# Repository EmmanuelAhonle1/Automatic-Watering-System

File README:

# Automatic Watering System

## Overview

The Automatic Watering System is a smart IoT solution for plant care, built using ESP8266 microcontrollers. The system provides automated plant monitoring and watering capabilities with a web-based interface for configuration and monitoring.

## Hardware Components

- ESP8266 Microcontroller
- DHT11 Temperature and Humidity Sensor (Pin D5)
- Capacitive Soil Moisture Sensor (Pin D6)
- VEML7700 Ambient Light Sensor (Pin D7)
- LC709203F Battery Level Sensor (Pin D4)
- RGB Status LED (Pins D0, D1, D2)
- All components are defined in `Pinouts.hpp`

## Features

### 1. WiFi Configuration and Management

- Captive portal for initial WiFi setup
- Automatic reconnection handling
- OTA (Over-the-Air) update support
- Access Point mode with DNS server for initial configuration
- Support for multiple network security types

### 2. Device Management

- Unique device naming system
- Persistent storage of device settings
- MAC address tracking
- JSON-based configuration storage

### 3. Sensor Integration

- Temperature and humidity monitoring
- Soil moisture level detection
- Ambient light measurement
- Battery level monitoring
- All sensor readings available through unified interface

### 4. Status Indication

RGB LED status indicators for:

- WiFi Connected (Blinking Blue)
- AP Mode (Solid Red)
- MySQL Server Connected (Solid Green)
- Connection Lost (Fast Red Blinking)
- Reconnecting (Purple Blinking)

### 5. Web Interface

Three main interfaces:

1. WiFi Configuration (`/wifi_config/`)

   - Network scanning
   - Connection management
   - Status display

2. User Authentication (`/intro_login/`)

   - User login
   - New user registration
   - Session management

3. Plant Registration (`/plant_registration/`)
   - Plant node configuration
   - Species selection
   - Customizable care parameters

## Software Architecture

### Core Components

1. **WiFi Manager** (`wifi_manager.hpp`, `wifi_manager.cpp`)

   - Handles all network connectivity
   - Manages access point and station modes
   - Implements captive portal
   - Handles OTA updates

2. **Device Manager** (`device_manager.hpp`, `device_manager.cpp`)

   - Manages device identification
   - Handles configuration storage
   - Coordinates settings updates

3. **Data Acquisition** (`dataAcquisition.hpp`, `dataAcquisition.cpp`)

   - Interfaces with all sensors
   - Provides unified data reading interface
   - Handles sensor calibration and thresholds

4. **Database Communication** (`DatabaseCommands.hpp`, `DatabaseCommands.cpp`)

   - Manages API interactions
   - Handles data synchronization
   - Implements connection monitoring

5. **RGB Status Handler** (`rgb_status.hpp`, `rgb_status.cpp`)
   - Manages visual feedback
   - Implements state machine for status indication
   - Handles LED control

### Web Interface

The system provides three main web interfaces:

1. **WiFi Configuration**

   - Network scanning and selection
   - Password input
   - Connection status display

2. **User Authentication**

   - Login interface
   - Registration form
   - Session management

3. **Plant Registration**
   - Plant species selection
   - Watering frequency configuration
   - Environmental threshold settings

## Setup and Configuration

### Initial Setup

1. Flash the ESP8266 with the firmware
2. Power on the device
3. Connect to the device's AP (Format: "PlantNode-XXXX")
4. Navigate to the captive portal
5. Configure WiFi settings

### Plant Registration

1. Login or create an account
2. Configure plant parameters:
   - Node name
   - Plant species
   - Watering frequency
   - Environmental thresholds
3. Save configuration

## API Integration

The system integrates with a REST API for:

- User authentication
- Plant node registration
- Settings synchronization
- Data logging

API endpoints are defined in `dbQueryCreator.hpp` and configured via `config.h`

## Development

### Requirements

- Arduino IDE or PlatformIO
- ESP8266 board support
- Required Libraries:
  - ESP8266WiFi
  - ESP8266WebServer
  - ArduinoJson
  - DHT sensor library
  - VEML7700 library
  - LC709203F library
  - RGBLed library

### Building

1. Clone the repository
2. Install required libraries
3. Configure `config.h` with API credentials
4. Build and flash to ESP8266

## Security Features

- Secure WiFi configuration
- Password protection
- Session management
- API authentication
- OTA update support

## Troubleshooting

### LED Status Indicators

- Solid Red: AP Mode (Initial setup required)
- Blinking Blue: Connected to WiFi
- Solid Green: Fully connected (WiFi + Database)
- Fast Red Blinking: Connection lost
- Purple Blinking: Attempting to reconnect

### Common Issues

1. Connection Failures

   - Check WiFi credentials
   - Verify API availability
   - Monitor LED status

2. Sensor Readings
   - Verify sensor connections
   - Check pin configurations
   - Validate sensor thresholds

## Contributing

1. Fork the repository
2. Create a feature branch
3. Submit a pull request

## License

[Add your license information here]

## Authors

[Add author information here]

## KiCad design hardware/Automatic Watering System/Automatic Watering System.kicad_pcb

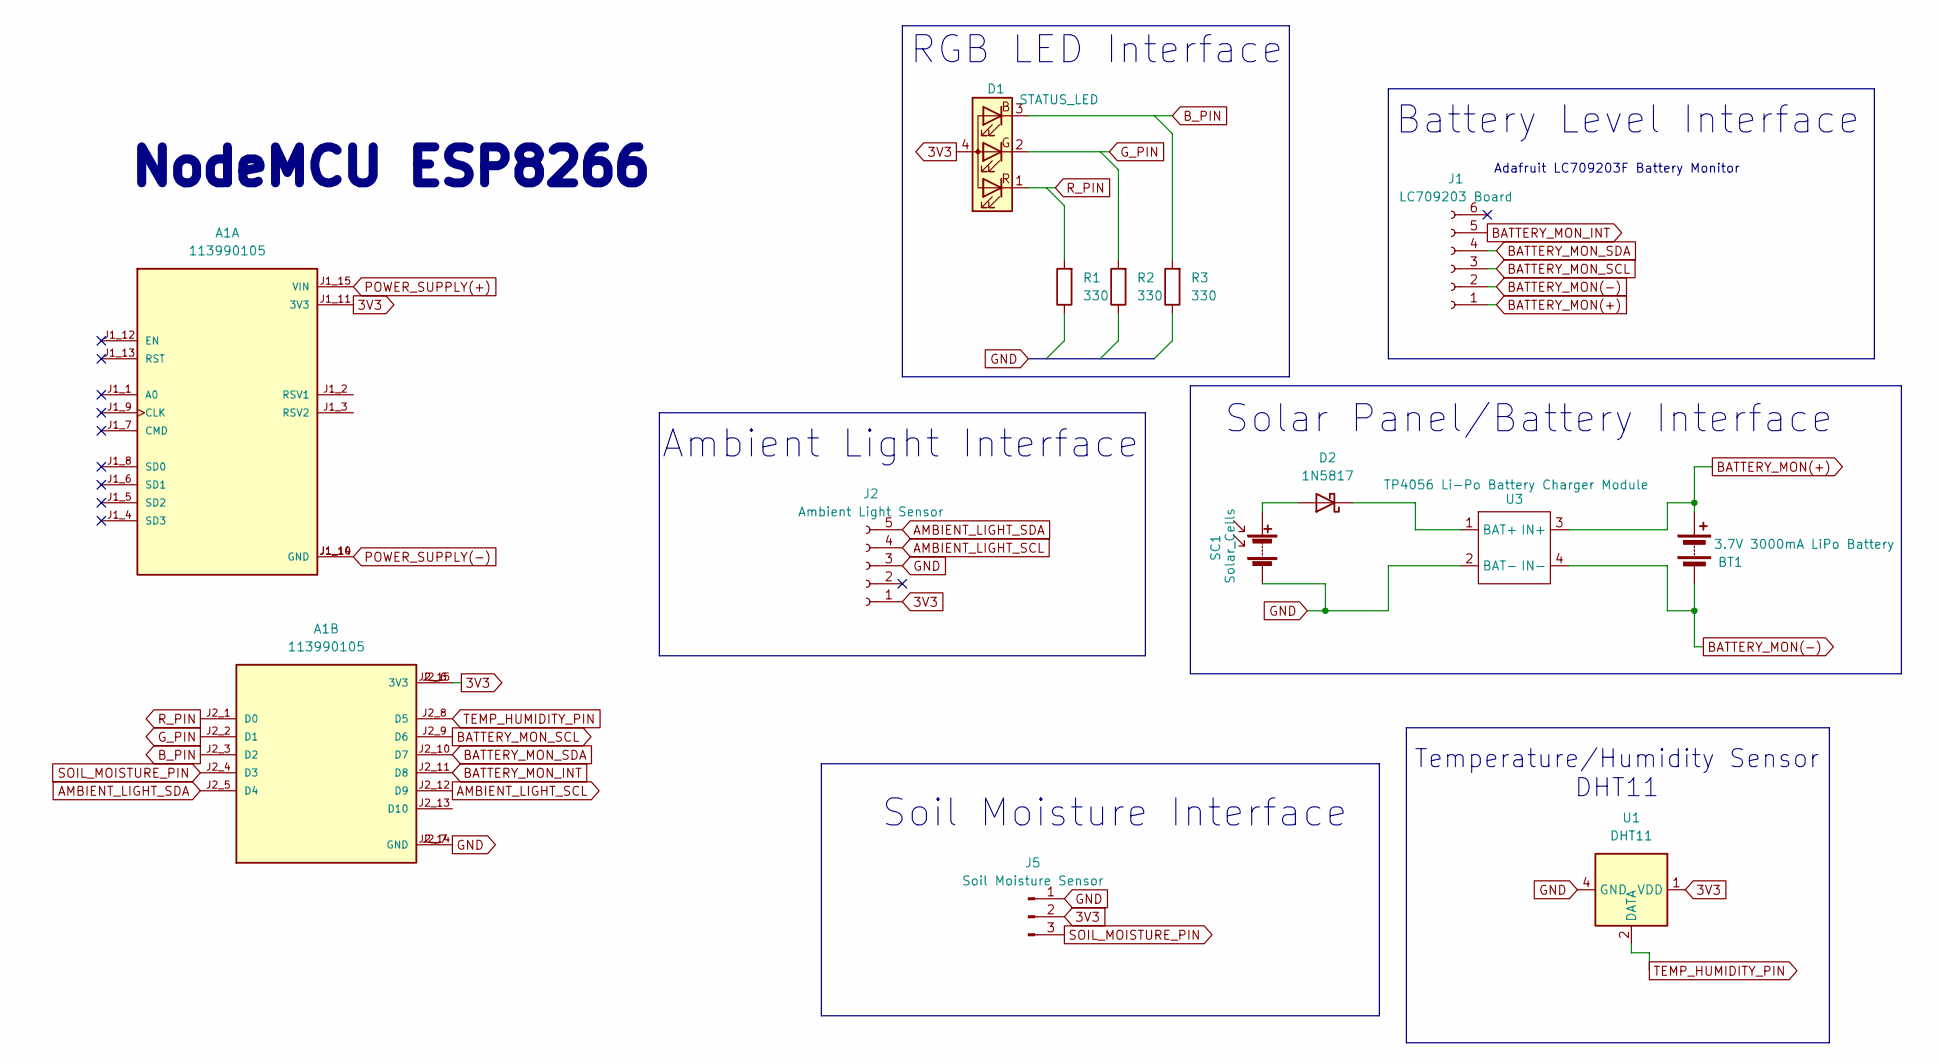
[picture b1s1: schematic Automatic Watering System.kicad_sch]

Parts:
A1: 113990105; SEEED_113990105; PARTREV N/A
BT1: 3.7V 3000mA LiPo Battery; JST_GH_SM02B-GHS-TB_1x02-1MP_P1.25mm_Horizontal
D1: STATUS_LED; PinSocket_1x04_P2.54mm_Vertical
D2: 1N5817; D_DO-41_SOD81_P10.16mm_Horizontal
J1: LC709203 Board; PinSocket_1x06_P2.54mm_Vertical
J2: Ambient Light Sensor; PinSocket_1x05_P2.54mm_Vertical
J5: Soil Moisture Sensor; PinHeader_1x03_P2.54mm_Vertical
R1, R2, R3: 330; R_Axial_DIN0204_L3.6mm_D1.6mm_P7.62mm_Horizontal
SC1: Solar_Cells; PinSocket_1x02_P1.00mm_Vertical_SMD_Pin1Left
U1: DHT11; Aosong_DHT11_5.5x12.0_P2.54mm
U3: TP4056 Li-Po Battery Charger Module; TP4056 1A Li-ion Battery Charging Module

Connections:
3V3: A1.J1_11 (3V3), A1.J2_6 (3V3), A1.J2_15 (3V3), D1.4 (A), J2.1, J5.2, U1.1 (VDD)
AMBIENT_LIGHT_SCL: A1.J2_12 (D9), J2.4
AMBIENT_LIGHT_SDA: A1.J2_5 (D4), J2.5
BATTERY_MON(+): BT1.1 (+), J1.1, U3.3 (IN+)
BATTERY_MON(-): BT1.2 (-), J1.2, U3.4 (IN-); also elsewhere on the board
BATTERY_MON_INT: A1.J2_11 (D8), J1.5
BATTERY_MON_SCL: A1.J2_9 (D6), J1.3
BATTERY_MON_SDA: A1.J2_10 (D7), J1.4
B_PIN: A1.J2_3 (D2), D1.3 (BK), R3.2
GND: A1.J2_7 (GND), A1.J2_14 (GND), J2.3, J5.1, SC1.2 (-), U1.4 (GND), U3.2 (BAT-)
G_PIN: A1.J2_2 (D1), D1.2 (GK), R2.2
unnamed: D2.2 (A), SC1.1 (+)
unnamed: D2.1 (K), U3.1 (BAT+)
POWER_SUPPLY(+): A1.J1_15 (VIN)
POWER_SUPPLY(-): A1.J1_10 (GND), A1.J1_14 (GND)
R_PIN: A1.J2_1 (D0), D1.1 (RK), R1.2
SOIL_MOISTURE_PIN: A1.J2_4 (D3), J5.3
TEMP_HUMIDITY_PIN: A1.J2_8 (D5), U1.2 (DATA)

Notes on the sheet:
Adafruit LC709203F Battery Monitor
Temperature/Humidity Sensor DHT11
Solar Panel/Battery Interface
NodeMCU ESP8266
RGB LED Interface
Soil Moisture Interface
Ambient Light Interface
Battery Level Interface

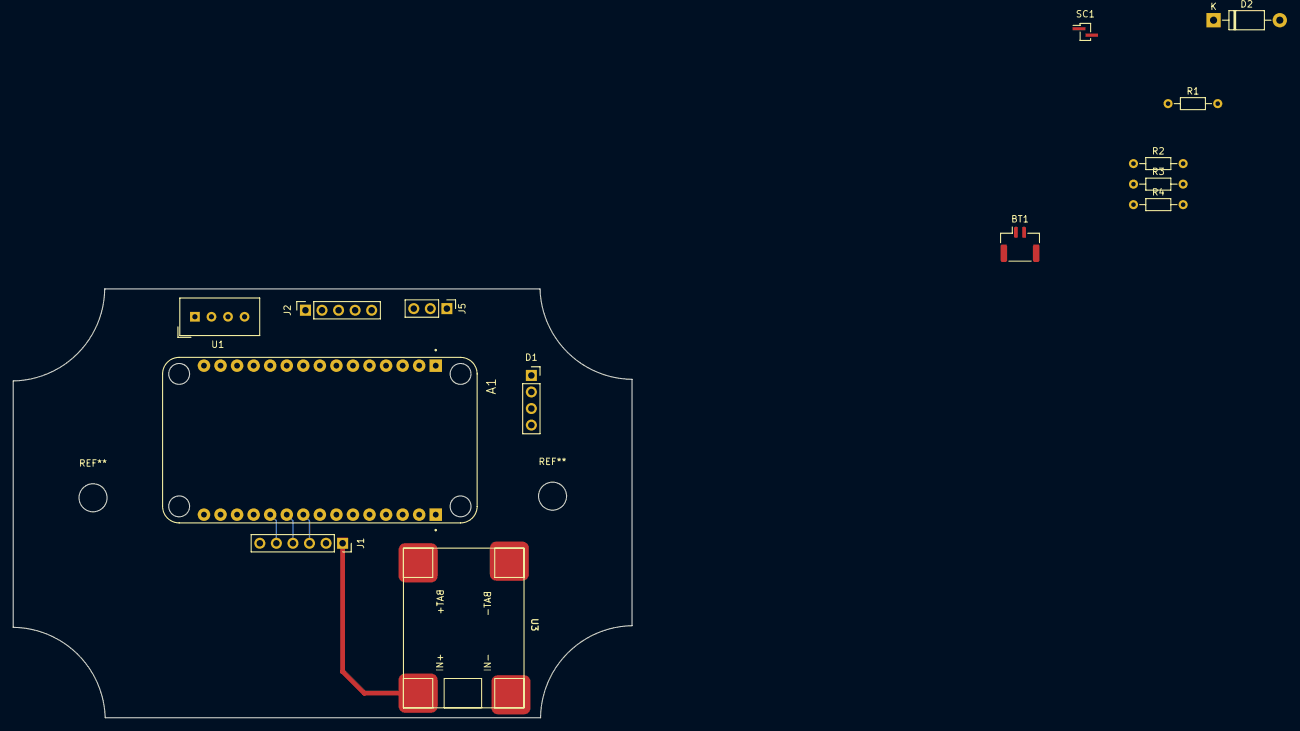
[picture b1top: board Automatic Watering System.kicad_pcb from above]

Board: 2 copper layers, 94.9 x 65.8 mm, 14 parts (0 on the bottom side), 17 nets.

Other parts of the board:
R4: 1.2k; R_Axial_DIN0204_L3.6mm_D1.6mm_P7.62mm_Horizontal

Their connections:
BATTERY_MON(-): R4.2; also elsewhere on the board

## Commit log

2024-09-23 adding new changes to code
2024-09-23 Stop tracking wifi_pass.hpp
2024-09-23 attempting to repair/hid wifi_pass
2024-09-23 msgt
2024-09-23 new commit
2024-09-23 removing server.crt and server.key
2024-09-23 updating .gitignore
2024-09-23 update wifi and password
2024-09-23 fixed OTA
2024-10-31 organized frontend code in data; updated wifi_driver.cpp correspondingly
2024-12-07 created state manager files
2024-12-07 completed stateManager
2024-12-07 complete revamp of backend
2024-12-07 new set
2024-12-07 PlantNode successfully pulls up portal on device, logs into specified network
2024-12-08 stable version of wifi_connect(1)
2024-12-12 preparation for AWS RDS MySQL db
2024-12-15 created outline for dataAcq files
2024-12-15 organized file directory
2024-12-15 added template SQL files for database
2024-12-15 updated platformio.ini and plantNode.cpp
2024-12-15 successful connection to MySQL
2024-12-15 updated begin() for wifi_manager to include web page files; added separate copies of modified MySQL_Connection files
2024-12-15 removed redundant setupAccessPoint() call and function in device_manager.cpp
2024-12-16 fixed reconnecting bug where ESP would attempt to reconnect to a network with empty bssid field in credentials.json
2024-12-16 added TimerInterrupt class and files
2024-12-17 persistence of credentials completed. Updated dataAcq for all sensors.
2024-12-18 updated queries and moved dbConnection files into separate folder
2024-12-18 adding OS files and app.py
2024-12-18 Added MySQL dependencies
2024-12-18 updating app.py to test os variables
2024-12-20 updating app.py to test os variables again!!
2024-12-20 dbConnection works properly
2024-12-20 DEVICE NAME FINALLY PERSISTS WOOHOOO!!!
2024-12-20 same update
2024-12-20 small bug fix
2024-12-22 plantNode name is updated/persisted within credentials.json
2024-12-22 added debug keys for print functions; updated pingDatabase to boolean
2024-12-23 setup ping for database and wifi
2024-12-23 using os environment variables for better security
2024-12-23 solid stopping point for tonight
2024-12-27 removing plantNodeManager
2024-12-28 currently working files
2024-12-29 properly store plant node settings in credentials.json
2024-12-31 created intro_login and plant_registration frontend files
2024-12-31 added routes for retrieving thresholds and watering frequencies
2024-12-31 adding CORS
2024-12-31 updated plant registration
2024-12-31 updated user creation
2025-01-01 updating frontend files
2025-01-01 current stable script
2025-01-01 include cookie handling for login
2025-01-01 updating verify endpoint
2025-01-01 stable login and plant registration
2025-01-01 updating CORS policy to allow any ip address formatted domain for the ESPs
2025-01-02 FINALLY CONFIGURED PERSISTENT SESSION
2025-01-02 reworking the newPlantNode endpoint
2025-01-02 WORKING INSERT FOR NEW PLANT NODE LESGOOO!!
2025-01-02 EVERYTHING IS FIXED!!!
2025-01-02 added debug config
2025-01-02 included RGB management
2025-01-03 save before changes
2025-01-04 added database command files, deleted dbConnection files, revamped wifiManager
2025-01-04 finally configured board to persist settings when connected to internet
2025-01-04 saving before experimenting with DatabaseCommands
2025-01-04 update RGB Status; centralized where database pings occur
2025-01-04 update completed for rgbStatus
2025-01-04 updated wifi-connect endpoint to store wifi and plant settings into credentials file
2025-01-04 included verbose readme for project
2025-01-04 remove readmae file
2025-01-04 updated sql files
2025-01-04 updating sql queries
2025-01-04 added setup readme and update main readme
2025-01-04 updated name
2025-01-04 adding reference to setup guide
2025-01-08 added hardware files and pinouts
2025-01-08 update readme according to new pinouts
2025-01-08 updating readme again
2025-01-28 edits to documents
2025-01-28 fully cleanerd version of code
2025-01-28 refactored DatabaseCommands files
2025-01-28 adding all setup files
2025-01-28 updated layout for React app
2025-01-29 updated CardContainer code
2025-01-29 save point
2025-01-29 removed todo for wifi_manager, successfully created cardcontainer component
2025-01-30 updated relevant files to jsx
2025-01-30 updated react js and sidebar for frontend
2025-01-30 added themes for web app
2025-10-28 necessary changes
2025-10-28 test changes
2025-10-28 new change
2025-10-29 changes made to Heroku
2025-10-29 added Sidebar component files
2025-10-29 updated App.jsx
2025-10-29 disabling Sidebar
2025-10-29 add requirements file for Automatic Watering System API
2026-02-15 add .vscode to .gitignore
2026-02-15 refactor: migrate microcontroller support from ESP8266 to ESP32
